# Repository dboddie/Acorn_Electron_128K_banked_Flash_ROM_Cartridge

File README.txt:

Introduction
------------

This repository provides schematic and circuit layout files for use with KiCad
describing a 128K Flash ROM cartridge suitable for use with the Acorn Electron
microcomputer's Plus 1 expansion unit. It is based on Paul Boddie's original
prototyping breakout cartridge.

The following resources are provided:

AcornElectronCartridge.kicad_pcb    The circuit board layout

AcornElectronCartridge.net          The netlist, generated from the schematic
                                    and distributed here for convenience

AcornElectronCartridge.pro          The KiCad project file

AcornElectronCartridge.sch          The circuit schematic providing the
                                    relationships between components

AcornElectron.lib                   Acorn Electron component library
                                    containing definitions for the edge
                                    connector (used by the schematic editor)

AcornElectron.pretty                Acorn Electron component footprint library
                                    containing definitions of the edge
                                    connector (used by the PCB editor)

BoardOutline                        Drawings defining the board outline plus
                                    descriptions of the drafting workflow and
                                    KiCad import considerations

Preparing the Schematic
-----------------------

Since the purpose of the board is merely that of routing signals, the
schematic is very simple. Connectors corresponding to the two sides of the
board edge connector are introduced, together with breakout connectors
corresponding to the exposed signals. Each edge connector pin is labelled and
a corresponding breakout connector pin is given a matching label. Thus, an
association is established between the edge connector pin and the breakout
pin.

The CvPcb tool in KiCad associates components with footprints. For convenient
prototyping, the breakout connectors are associated with headers with 0.1 inch
pin spacing (or pitch). The edge connectors are associated with specially
designed footprints for the Acorn Electron cartridge provided by the Acorn
Electron footprint component library (AcornElectron.pretty).

Preparing the Board Outline
---------------------------

In order to produce a board of the right shape (or indeed of any shape), a
board outline must first be produced. The BoardOutline directory contains
documentation of the workflow involved in applying measurements used by other
cartridges to produce a suitable drawing (cartridge_board_rear.dxf) which can
then be used in KiCad (and by subsequent production tools) to establish the
correct positions and dimensions of board features such as mounting holes and
the edge connector portion of the board.

This board outline is exported as DXF (using version 14 in Inkscape) and
imported into KiCad to provide the basis of the board itself. The outline is
imported into the Edge.Cuts layer, indicating that it shall be used to direct
cutting tools to define the shape of the board. In order to align the outline
with a grid using 0.127mm (0.05 inch) units, the origin of the outline is
positioned at (60.445mm, 127mm). More information about the calculations can
be found in the BoardOutline documentation.

Preparing the Board Layout
--------------------------

Each component must be positioned appropriately on the board for it to make
any physical sense. The edge connector footprints must be placed on each side
of the protruding portion of the board, and the breakout connector footprints
must be placed high enough up on the board to be accessible when the cartridge
is inserted into the Plus 1. Beyond this, board layout is mostly a matter of
routing tracks between connectors and avoiding board features such as mounting
holes and the board edges.

Design Rules and Production
---------------------------

The original prototyping cartridge was sent to OSHPark for production. Thus,
the design rules for OSHPark were added to the project configuration. Such
rules can be found here:

http://docs.oshpark.com/services/two-layer/
http://docs.oshpark.com/design-tools/kicad/kicad-design-rules/

Contact, Copyright and Licence Information
------------------------------------------

The author can be contacted at the following e-mail address:

david@boddie.org.uk

Copyright and licence information can be found in the docs directory - see
docs/COPYING.txt and docs/gpl-3.0.txt for more information.

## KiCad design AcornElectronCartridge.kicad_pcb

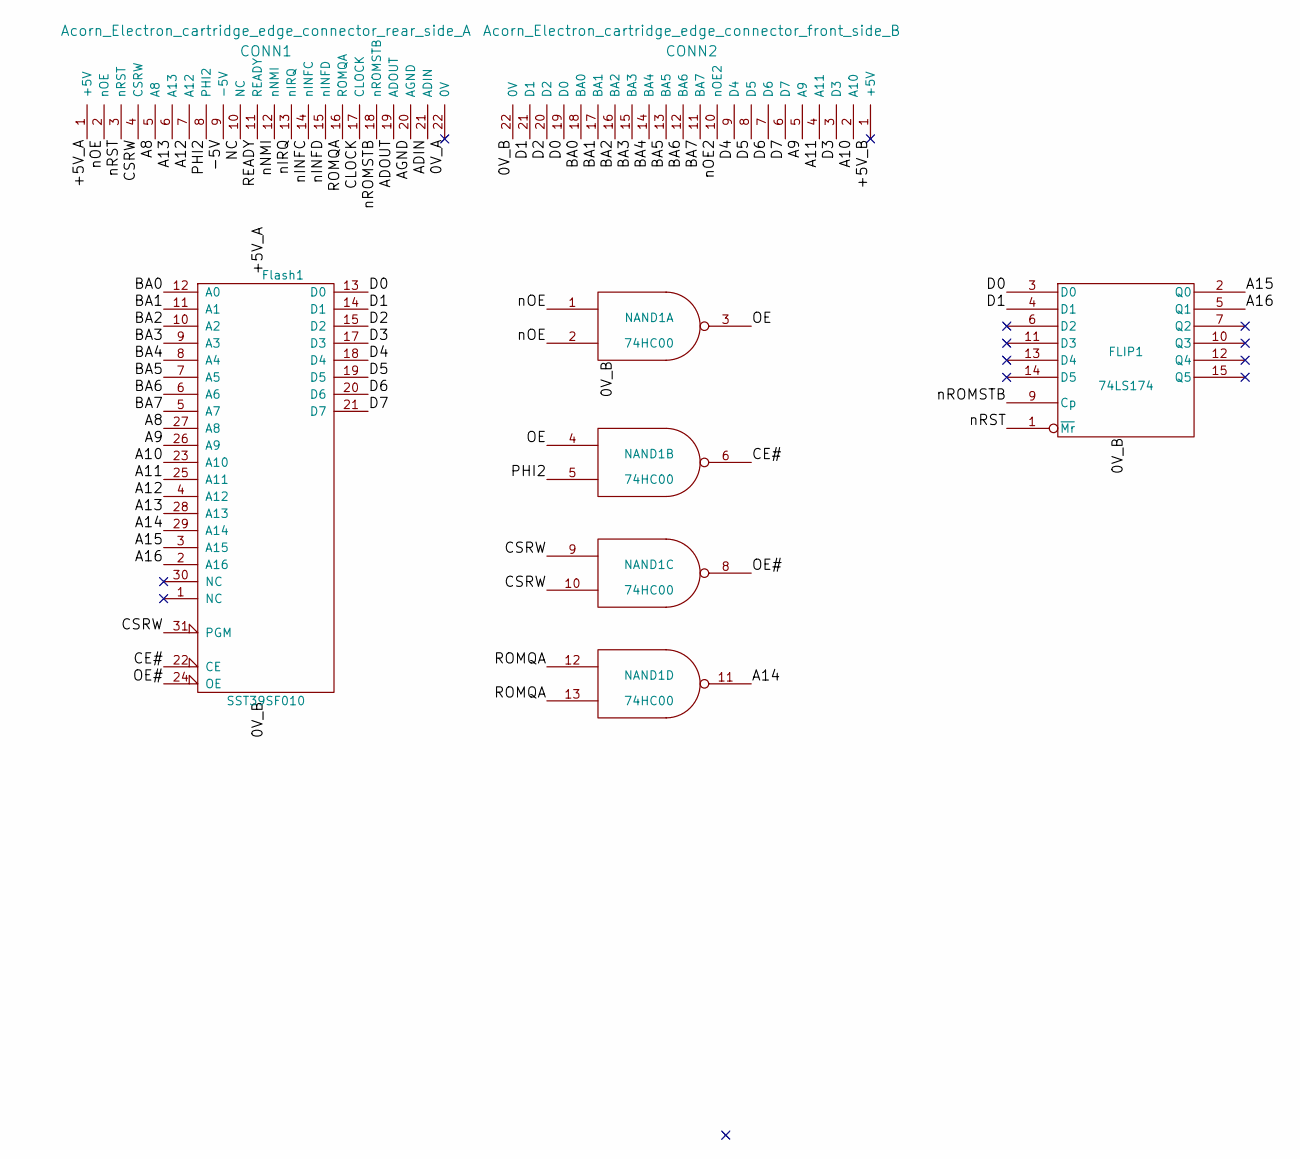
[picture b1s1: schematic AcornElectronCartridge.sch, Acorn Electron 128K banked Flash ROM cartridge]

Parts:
CONN1: Acorn_Electron_cartridge_edge_connector_rear_side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; Acorn_Electron_cartridge_edge_connector_rear
CONN2: Acorn_Electron_cartridge_edge_connector_front_sid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; Acorn_Electron_cartridge_edge_connector_front
FLIP1: 74LS174; DIP-16_W7.62mm_Socket
Flash1: SST39SF010; DIP-32_W15.24mm_Socket
NAND1: 74HC00; DIP-14_W7.62mm_Socket

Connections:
/0V_A: CONN1.22 (0V)
/+5V_B: CONN2.1 (+5V)
/-5V: CONN1.9 (-5V)
/A8: CONN1.5 (A8), Flash1.27 (A8)
/A9: CONN2.5 (A9), Flash1.26 (A9)
/A10: CONN2.2 (A10), Flash1.23 (A10)
/A11: CONN2.4 (A11), Flash1.25 (A11)
/A12: CONN1.7 (A12), Flash1.4 (A12)
/A13: CONN1.6 (A13), Flash1.28 (A13)
/A14: Flash1.29 (A14), NAND1.11
/A15: FLIP1.2 (Q0), Flash1.3 (A15)
/A16: FLIP1.5 (Q1), Flash1.2 (A16)
/ADIN: CONN1.21 (ADIN)
/ADOUT: CONN1.19 (ADOUT)
/AGND: CONN1.20 (AGND)
/BA0: CONN2.18 (BA0), Flash1.12 (A0)
/BA1: CONN2.17 (BA1), Flash1.11 (A1)
/BA2: CONN2.16 (BA2), Flash1.10 (A2)
/BA3: CONN2.15 (BA3), Flash1.9 (A3)
/BA4: CONN2.14 (BA4), Flash1.8 (A4)
/BA5: CONN2.13 (BA5), Flash1.7 (A5)
/BA6: CONN2.12 (BA6), Flash1.6 (A6)
/BA7: CONN2.11 (BA7), Flash1.5 (A7)
/CE#: Flash1.22 (CE), NAND1.6
/CLOCK: CONN1.17 (CLOCK)
/CSRW: CONN1.4 (CSRW), Flash1.31 (PGM), NAND1.9, NAND1.10
/D0: CONN2.19 (D0), FLIP1.3 (D0), Flash1.13 (D0)
/D1: CONN2.21 (D1), FLIP1.4 (D1), Flash1.14 (D1)
/D2: CONN2.20 (D2), Flash1.15 (D2)
/D3: CONN2.3 (D3), Flash1.17 (D3)
/D4: CONN2.9 (D4), Flash1.18 (D4)
/D5: CONN2.8 (D5), Flash1.19 (D5)
/D6: CONN2.7 (D6), Flash1.20 (D6)
/D7: CONN2.6 (D7), Flash1.21 (D7)
/NC: CONN1.10 (NC)
/OE: NAND1.3, NAND1.4
/OE#: Flash1.24 (OE), NAND1.8
/PHI2: CONN1.8 (PHI2), NAND1.5
/READY: CONN1.11 (READY)
/ROMQA: CONN1.16 (ROMQA), NAND1.12, NAND1.13
/nINFC: CONN1.14 (nINFC)
/nINFD: CONN1.15 (nINFD)
/nIRQ: CONN1.13 (nIRQ)
/nNMI: CONN1.12 (nNMI)
/nOE: CONN1.2 (nOE), NAND1.1, NAND1.2
/nOE2: CONN2.10 (nOE2)
/nROMSTB: CONN1.18 (nROMSTB), FLIP1.9 (Cp)
/nRST: CONN1.3 (nRST), FLIP1.1 (~Mr)
GND: CONN2.22 (0V), FLIP1.8 (GND), Flash1.16 (GND), NAND1.7 (GND)
VCC: CONN1.1 (+5V), FLIP1.16 (VCC), Flash1.32 (VCC), NAND1.14 (VCC)

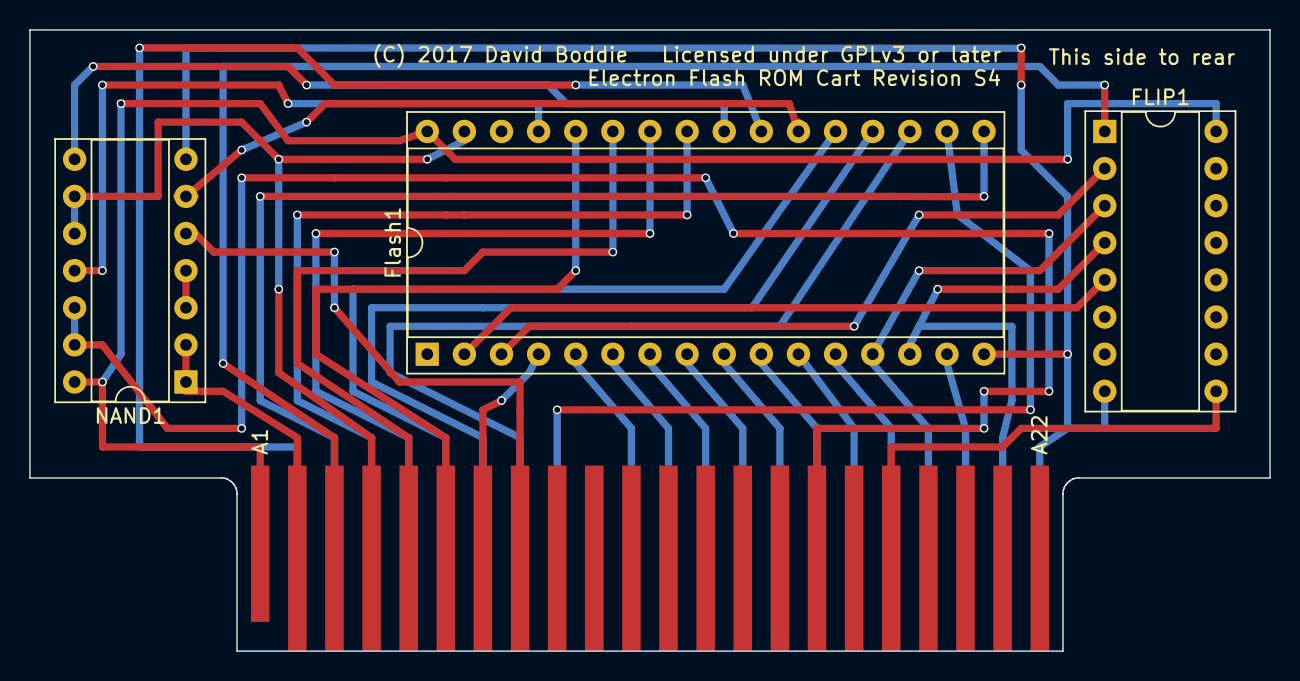
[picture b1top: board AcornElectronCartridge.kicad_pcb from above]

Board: 2 copper layers, 84.9 x 42.5 mm, 5 parts (1 on the bottom side), 36 nets.

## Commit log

2017-01-18 An Acorn Electron prototyping/breakout cartridge.
2017-01-19 Introduced separate front and rear edge connector footprints. Moved various labels on the edge connector components and footprints, also changing the visible name labels to use spaces instead of unde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
2017-01-19 Changed the front edge connector to be associated with B.Cu rather than F.Cu (with which the rear edge connector is associated). None of the pad layers are changed.
2017-01-19 Adjusted "keep out" regions, moving some tracks closer to avoid these regions.
2017-01-24 Added tag oshpark-648KdmKd for changeset bc230b5ea2ea
2017-02-16 Added project metadata to the schematic and board files.
2017-02-16 Added the component footprint library to the project itself for convenience.
2017-02-16 Added board outline details previously retained by the AcornElectron repository in its CartridgePCB subdirectory.
2017-02-16 Added documentation, copyright and licensing information.
2017-02-16 Updated the netlist. Various library settings and metadata were also updated.
2017-02-16 Tested Gerber output with only metadata changing.
2017-02-18 Fixed large hole width labels.
2017-03-19 Added copyright notice guidelines.
2017-10-02 Removed footprints, pads, vias and tracks. Changed labels to reflect the new use for the design.
2017-10-03 Finished the basic design.
2017-10-03 Renamed components. Tidied up a little.
2017-10-03 More minor improvements.
2017-10-03 Updated the instructions to refer to the current design.
2017-10-03 Moved two tracks to the other side of the board for clarity.
2017-10-07 Removed the pads and added flip-flops to support the use of the FC73 paging register for software-enabled bank selection.
2017-10-07 Moved a via away from a silkscreen line.
2017-10-07 Removed an unused track.
2017-10-07 Tidied up tracks to leave more space between silkscreen markings and vias. Only used one +5V line and kept the 0V lines separate.
2017-10-07 Added tag r1 for changeset 516938df70fc
2017-10-08 Placed all tracks linked to flash ROM pads on the same side of the board.
2017-10-08 Added tag r1 for changeset 515886f2eab2
2017-10-08 Left more room between pads and tracks.
2017-10-08 Added tag r1 for changeset d59a0889360b
2017-10-08 Moved a via away from silkscreen text.
2017-10-08 Added tag r1 for changeset 7c1f280cf9f0
2017-10-08 Tweaking a via position.
2017-10-08 Added tag r1 for changeset 00e4def608ea
2017-10-11 Started to modify the board to make it smaller.
2017-10-11 An intermediate version of a smaller cartridge.
2017-10-11 Made space at the top of the board.
2017-10-12 Finished a first draft of the smaller cartridge design.
2017-10-12 Added tag smaller-r1 for changeset 0492b022c160
2017-10-12 Placed the smaller chips beside the flash ROM.
2017-10-12 Added tag smaller-r2 for changeset 19663525557b
2017-10-12 Put all the chips on the same side of the board.
2017-10-12 Added tag smaller-r3 for changeset eebd89988d9f
2017-10-13 Updated the board outline and tidied up tracks and labels.
2017-10-13 Added tag smaller-r4 for changeset 87ec821937d9
2017-10-13 Updated the description in the schematic.
2017-10-19 Updated the copyright information.

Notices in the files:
AcornElectronCartridge.kicad_pcb:
Design licensed under the terms of the GNU General Public License version 3 or later.
(C) 2017 David Boddie Licensed under GPLv3 or later
